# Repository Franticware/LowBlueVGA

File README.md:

# LowBlueVGA
Adjustable low blue light filter circuit for VGA interface.

Here you can find more information: https://www.franticware.com/blog-low-blue-vga

There is also a video of the device being assembled: https://www.youtube.com/watch?v=y3SrTiCourk

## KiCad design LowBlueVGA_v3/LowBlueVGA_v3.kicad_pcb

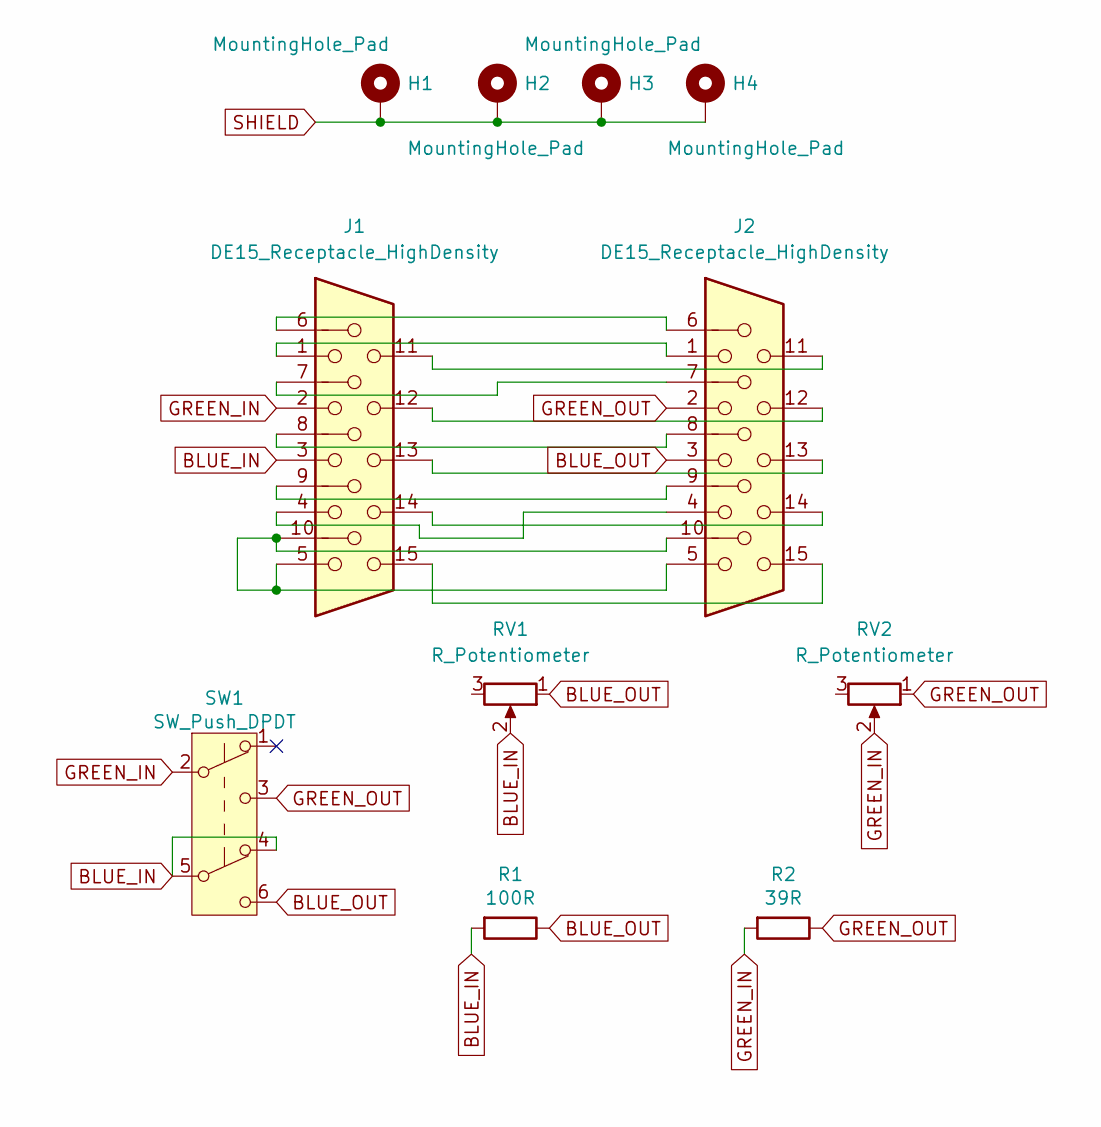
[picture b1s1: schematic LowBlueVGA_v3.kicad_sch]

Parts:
H1, H2, H3, H4: MountingHole_Pad; MountingHole_3.2mm_M3_ISO7380_Pad
J1, J2: DE15_Receptacle_HighDensity; DSUB-15-HD_Female_Horizontal_P2.29x2.54mm_EdgePinOffset9.40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
R1: 100R; R_1206_3216Metric
R2: 39R; R_1206_3216Metric
RV1, RV2: R_Potentiometer; Potentiometer_Vishay_T93YA_Vertical
SW1: SW_Push_DPDT; SW_E-Switch_EG1271_DPDT

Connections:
BLUE_IN: J1.3, R1.2, RV1.2, SW1.4 (A), SW1.5 (B)
BLUE_OUT: J2.3, R1.1, RV1.1, SW1.6 (C)
GREEN_IN: J1.2, R2.2, RV2.2, SW1.2 (B)
GREEN_OUT: J2.2, R2.1, RV2.1, SW1.3 (C)
unnamed: J1.1, J2.1
unnamed: J1.4, J2.4
unnamed: J1.6, J2.6
unnamed: J1.7, J2.7
unnamed: J1.8, J2.8
unnamed: J1.9, J2.9
unnamed: J1.5, J1.10, J2.5, J2.10
unnamed: J1.11, J2.11
unnamed: J1.12, J2.12
unnamed: J1.13, J2.13
unnamed: J1.14, J2.14
unnamed: J1.15, J2.15
SHIELD: H1.1, H2.1, H3.1, H4.1

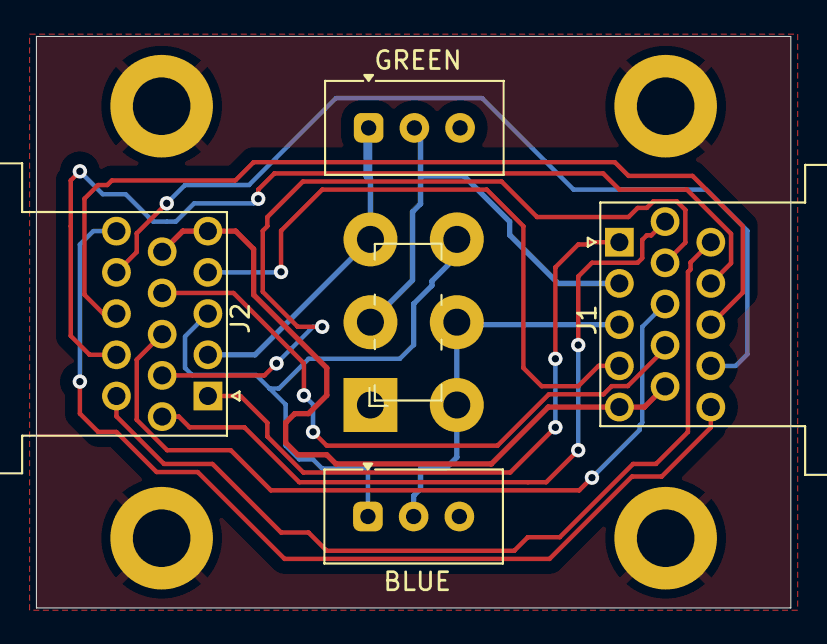
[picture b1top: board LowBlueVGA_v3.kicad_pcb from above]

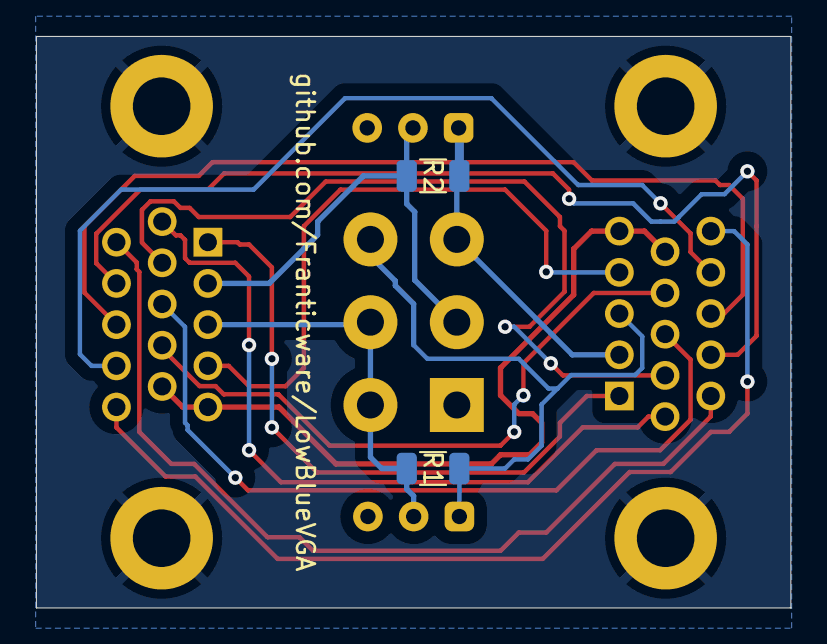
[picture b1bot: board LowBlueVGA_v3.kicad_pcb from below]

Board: 2 copper layers, 41.9 x 31.8 mm, 11 parts (2 on the bottom side), 17 nets.

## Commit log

2024-12-09 PCB v3
